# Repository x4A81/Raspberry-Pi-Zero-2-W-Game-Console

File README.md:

# Raspberry-Pi-Zero-2-W-Game-Console
This is a handheld game console based on Raspberry Pi Zero 2 W and RetroPie.
The hardware included are:
- 3.5" LCD display
- Raspberry Pi Zero 2 W
- 3.7V 3000mAh lipo battery
- TP4056 USB-C 1A lipo charger board
- DC-DC boost converter
- I2S PCM5102A DAC with Headphone Jack

To use the game console you first have to flash RetroPie to a microSD card and then insert it into the Pi.
I made this project as I wanted to play some retro games but I didn't want to purchase multiple consoles. So I decided that I wanted to build one!
Here is the schematic, PCB and case that I had to design.

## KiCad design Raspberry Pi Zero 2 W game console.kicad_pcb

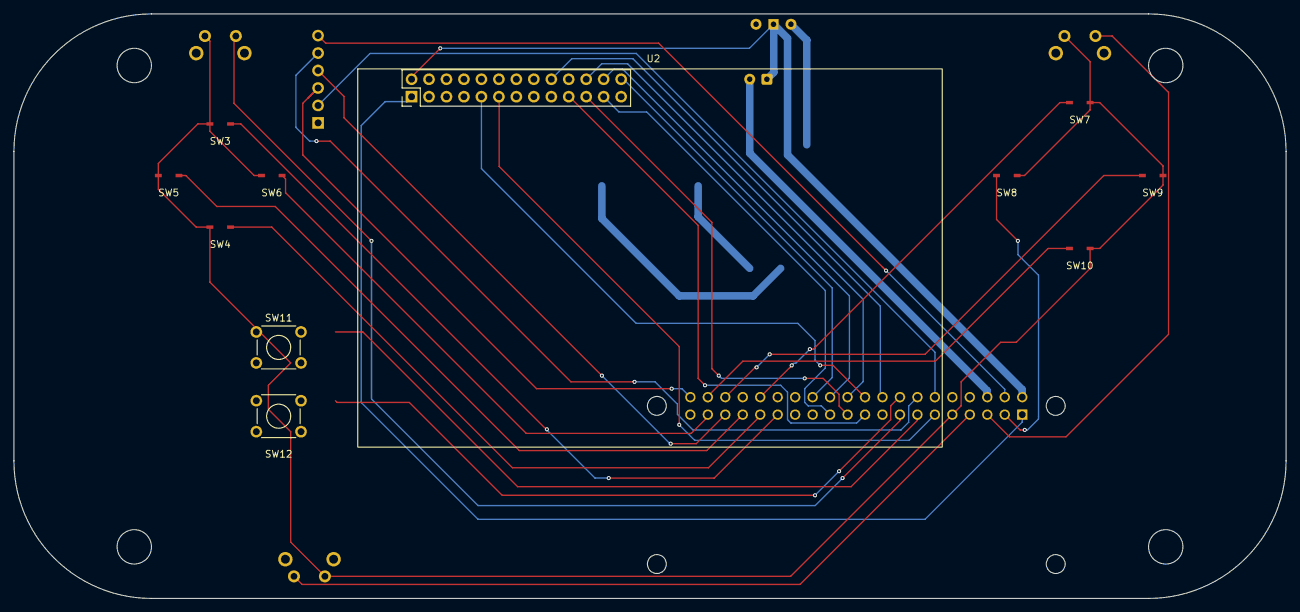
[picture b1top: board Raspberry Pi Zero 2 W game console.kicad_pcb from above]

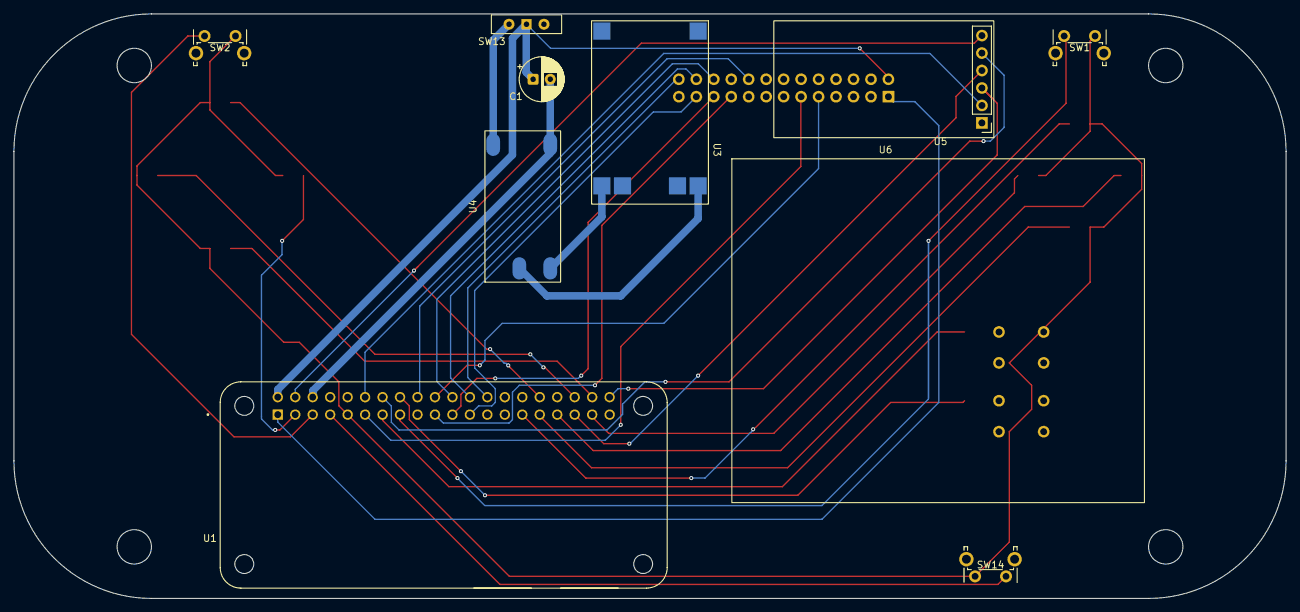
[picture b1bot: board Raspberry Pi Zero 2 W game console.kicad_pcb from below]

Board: 2 copper layers, 185.0 x 85.0 mm, 21 parts (10 on the bottom side), 34 nets.

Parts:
C1: C_Polarized_470uf; CP_Radial_D6.3mm_P2.50mm
SW1: L; SW_Tactile_SPST_Angled_PTS645Vx58-2LFS
SW2: R; SW_Tactile_SPST_Angled_PTS645Vx58-2LFS
SW3: D_UP; Button_Contact
SW4: D_DOWN; Button_Contact
SW5: D_LEFT; Button_Contact
SW6: D_RIGHT; Button_Contact
SW7: X; Button_Contact
SW8: Y; Button_Contact
SW9: A; Button_Contact
SW10: B; Button_Contact
SW11: Select; SW_TH_Tactile_Omron_B3F-100x
SW12: Start; SW_TH_Tactile_Omron_B3F-100x
SW13: SW_SPDT; SW_Slide-03_Wuerth-WS-SLTV_10x2.5x6.4_P2.54mm
SW14: SYS; SW_Tactile_SPST_Angled_PTS645Vx58-2LFS
U1: RASPBERRY_PI_ZERO_2_W; MODULE_RASPBERRY_PI_ZERO_2_W
U2: LCD_3.5"; LCD_Screen
U3: LiPo_Charger; LiPo Charger 38x17
U4: Boost Converter; Boost_Converter
U5: BAT; LipoBattery50x60
U6: Audio board; Audio_Board

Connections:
/3V3_Pin1: U1.1 (3V3_1), U2.1 (3.3V)
/5V_Pin2: C1.1, SW13.1 (A), U1.2 (5V_2), U2.2 (5V)
/5V_Pin4: U1.4 (5V_4), U6.6 (VIN)
/A_Pin36: SW9.1, U1.36 (GPIO16)
/BCK_Pin12: U1.12 (GPIO18/GPIO_GEN1), U6.2 (BCK)
/B_Pin38: SW10.1, U1.38 (GPIO20)
/DIN_Pin40: U1.40 (GPIO21), U6.3 (DIN)
/DWN_Pin31: SW4.2, U1.31 (GPIO6)
/GND_Pin6: C1.2, U1.6 (GND_6), U4.4 (OUT-)
/GND_Pin9: SW1.2, SW2.2, SW3.1, SW4.1, SW5.1, SW6.1, SW7.2, SW8.2, SW9.2, SW10.2, SW11.2, SW12.2, SW14.2, U1.9 (GND_9)
/GND_Pin14: U1.14 (GND_14), U6.5 (GND)
/GND_Pin20: U1.20 (GND_20), U2.9 (GND)
/LCD_CS_Pin24: U1.24 (GPIO8/SPI_~CE0), U2.24 (LCD_CS)
/LCD_RS_Pin18: U1.18 (GPIO24/GPIO_GEN5), U2.18 (LCD_RS)
/LCD_SCK_Pin23: U1.23 (GPIO11/SPI_SCLK), U2.23 (LCD_SCK/TP_SCK)
/LCD_SI_Pin19: U1.19 (GPIO10/SPI_MOSI), U2.19 (LCD_SI/TP_SI)
/LEFT_Pin33: SW5.2, U1.33 (GPIO13)
/LRCK_Pin35: U1.35 (GPIO19), U6.4 (LCK)
/L_Pin15: SW1.1, U1.15 (GPIO22/GPIO_GEN3)
/RGHT_Pin37: SW6.2, U1.37 (GPIO26)
/RST_Pin22: U1.22 (GPIO25/GPIO_GEN6), U2.22 (RST)
/R_Pin5: SW2.1, U1.5 (GPIO3/SCL)
/SC_Pin13: SW11.1, U1.13 (GPIO27/GPIO_GEN2)
/START_Pin16: SW12.1, U1.16 (GPIO23/GPIO_GEN4)
/SYS_Pin7: SW14.1, U1.7 (GPIO4/GPIO_GCLK)
/TP_CS_Pin26: U1.26 (GPIO7/SPI_~CE1), U2.26 (TP_CS)
/TP_IRQ_Pin11: U1.11 (GPIO17/GPIO_GEN0), U2.11 (TP_IRQ)
/TP_SO_Pin21: U1.21 (GPIO9/SPI_MISO), U2.21 (TP_SO)
/UP_Pin29: SW3.2, U1.29 (GPIO5)
/X_Pin32: SW7.1, U1.32 (GPIO12)
/Y_Pin3: SW8.1, U1.3 (GPIO2/SDA1)
unnamed: SW13.2 (B), U4.3 (OUT+)
unnamed: U3.3 (OUT+), U4.1 (IN+)
unnamed: U3.6 (OUT-), U4.2 (IN-)

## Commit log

2026-03-02 Updated README with project details and images.
2026-03-02 Added KiCad files
